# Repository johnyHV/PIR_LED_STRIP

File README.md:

# PIR_LED_STRIP

Control board with PIR senzor, IR remote control and LED strip. LED strip contain addressable SK6812 RGBW LEDs. It is a board for corridor lighting when motion is detected

Animation

Color presentation

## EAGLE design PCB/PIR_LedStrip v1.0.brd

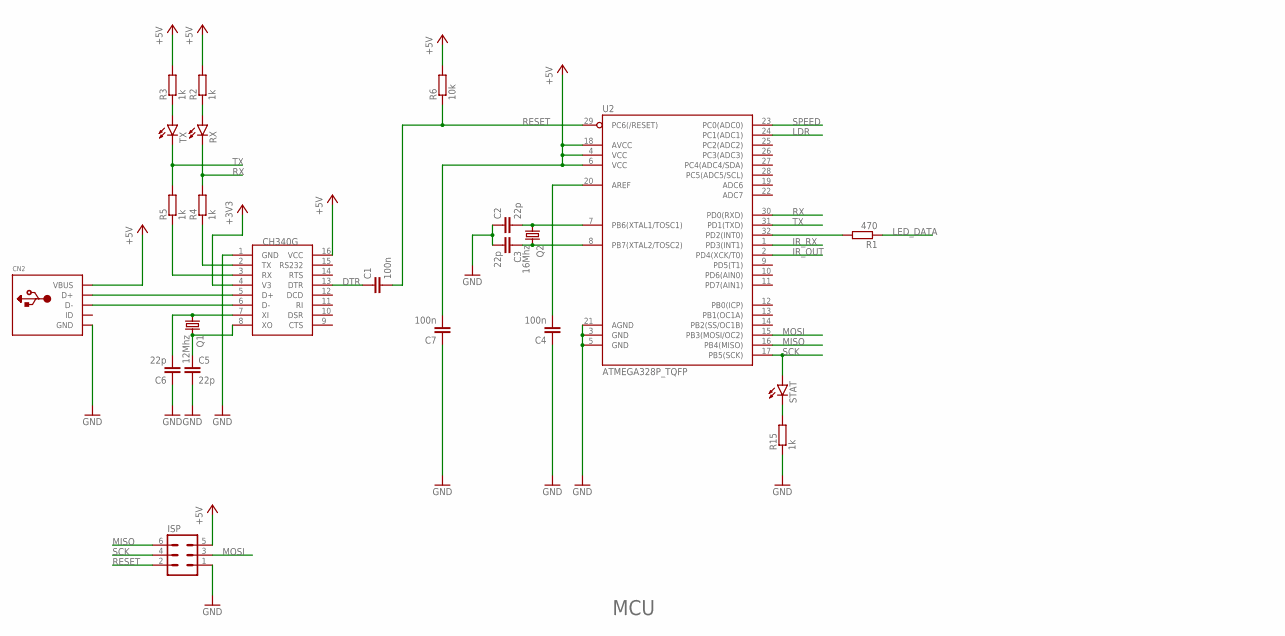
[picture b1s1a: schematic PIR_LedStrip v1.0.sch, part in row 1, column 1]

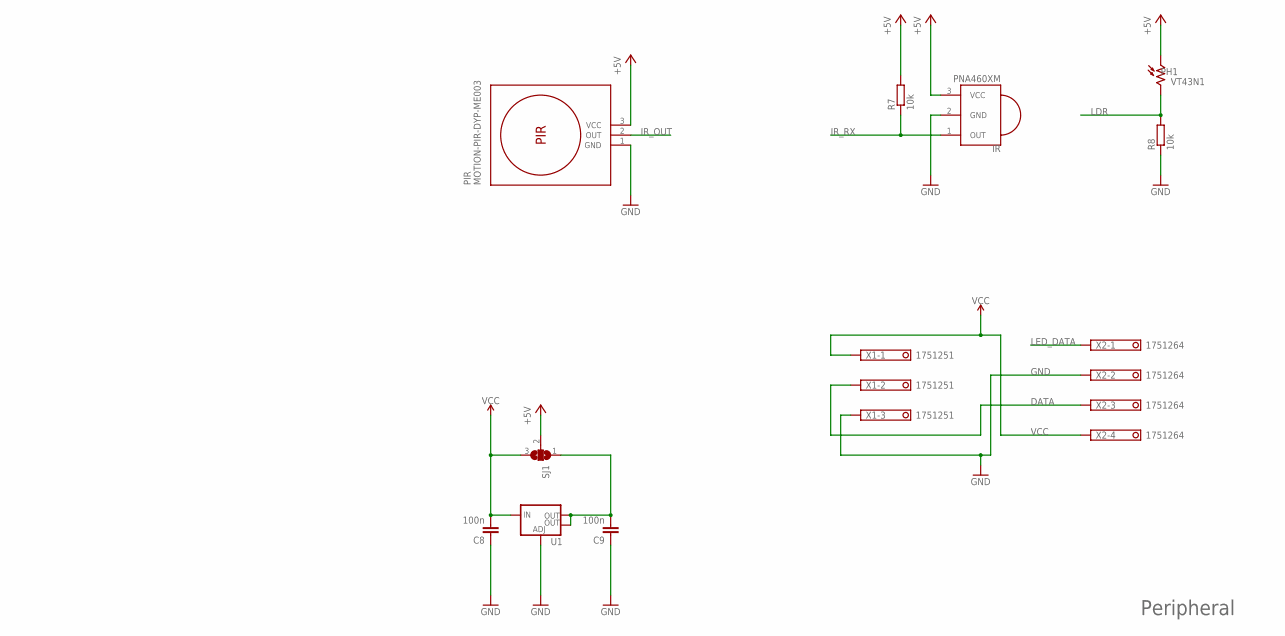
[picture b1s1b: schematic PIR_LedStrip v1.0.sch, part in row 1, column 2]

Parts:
C1, C4, C7, C8, C9: 100n; C0603
C2, C3, C5, C6: 22p; C0603
CN2: USBMINIB; USB-MINIB
IR: PNA460XM
ISP: MA03-2
PH1: VT43N1; VT400
PIR: MOTION-PIR-DYP-ME003
Q1: 12Mhz; HC49UP
Q2: 16Mhz; HC49UP
R1: 470; R0603
R2, R3, R4, R5, R15: 1k; R0603
R6, R7, R8: 10k; R0603
RX: LEDSML0805; SML0805
SJ1: SJ2W; SJ_2
STAT: LEDSML0805; SML0805
TX: LEDSML0805; SML0805
U1: V_REG_LM1117SOT223; SOT223
U2: ATMEGA328P_TQFP; TQFP32-08
U$1: CH340G; SOIC16
X1: 1751251
X2: 1751264

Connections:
+3V3: U$1.4 (V3)
+5V: C7.2, CN2.VBUS, IR.3 (VCC), ISP.5, PH1.1, PIR.3 (VCC), R2.2, R3.2, R6.2, R7.2, SJ1.2, U2.4 (VCC), U2.6 (VCC), U2.18 (AVCC), U$1.16 (VCC)
DATA: X1.2, X2.3
DTR: C1.1, U$1.13 (DTR)
GND: C2.1, C3.2, C4.1, C5.2, C6.1, C7.1, C8.1, C9.1, CN2.GND, IR.2 (GND), ISP.1, PIR.1 (GND), R8.1, R15.1, U1.1 (ADJ), U2.3 (GND), U2.5 (GND), U2.21 (AGND), U$1.1 (GND), X1.3, X2.2
IR_OUT: PIR.2 (OUT), U2.2 (PD4(XCK/T0))
IR_RX: IR.1 (OUT), R7.1, U2.1 (PD3(INT1))
LDR: PH1.2, R8.2, U2.24 (PC1(ADC1))
LED_DATA: R1.1, X2.1
MISO: ISP.6, U2.16 (PB4(MISO))
MOSI: ISP.3, U2.15 (PB3(MOSI/OC2))
unnamed: CN2.D+, U$1.5 (D+)
unnamed: R1.2, U2.32 (PD2(INT0))
unnamed: CN2.D-, U$1.6 (D-)
unnamed: R5.1, U$1.3 (RX)
unnamed: R4.1, U$1.2 (TX)
unnamed: C2.2, Q2.1, U2.7 (PB6(XTAL1/TOSC1))
unnamed: C6.2, Q1.1, U$1.7 (XI)
unnamed: C5.1, Q1.2, U$1.8 (XO)
unnamed: R2.1, RX.A
unnamed: R3.1, TX.A
unnamed: C3.1, Q2.2, U2.8 (PB7(XTAL2/TOSC2))
unnamed: C4.2, U2.20 (AREF)
unnamed: C9.2, SJ1.1, U1.2 (OUT), U1.4 (OUT)
unnamed: R15.2, STAT.C
RESET: C1.2, ISP.2, R6.1, U2.29 (PC6(/RESET))
RX: R4.2, RX.C, U2.30 (PD0(RXD))
SCK: ISP.4, STAT.A, U2.17 (PB5(SCK))
SPEED: U2.23 (PC0(ADC0))
TX: R5.2, TX.C, U2.31 (PD1(TXD))
VCC: C8.2, SJ1.3, U1.3 (IN), X1.1, X2.4

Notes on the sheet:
MCU
Peripheral

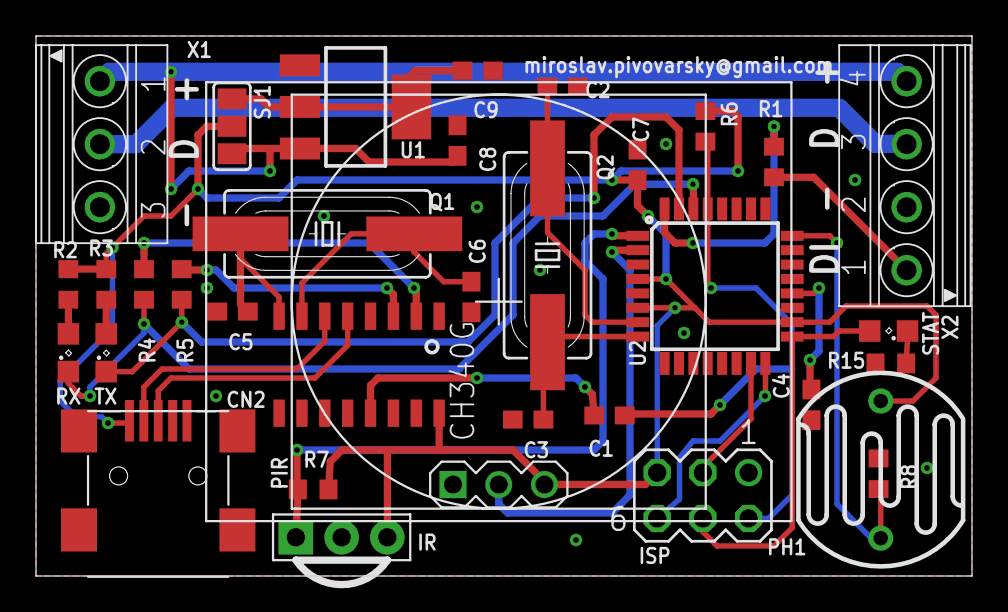
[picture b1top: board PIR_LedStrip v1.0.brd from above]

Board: 2 copper layers, 52.0 x 30.0 mm, 34 parts (0 on the bottom side), 29 nets.

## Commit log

2020-10-13 [PCB]
    - add PCB and schematic
2020-10-13 [docu]
    - add documentation
2020-10-13 [SW]
    - add source code
2020-11-06 [SW]
    - move constant string to F memory

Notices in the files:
parts and their libraries:
acs712: Released under the Creative Commons Attribution 4.0 International License: http://creativecommons.org/licenses/by/4.0
SparkFun-IC-Power: Licensing: Creative Commons ShareAlike 4.0 International - https://creativecommons.org/licenses/by-sa/4.0
